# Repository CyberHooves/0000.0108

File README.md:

# 0000.0108
Headphone amplifier

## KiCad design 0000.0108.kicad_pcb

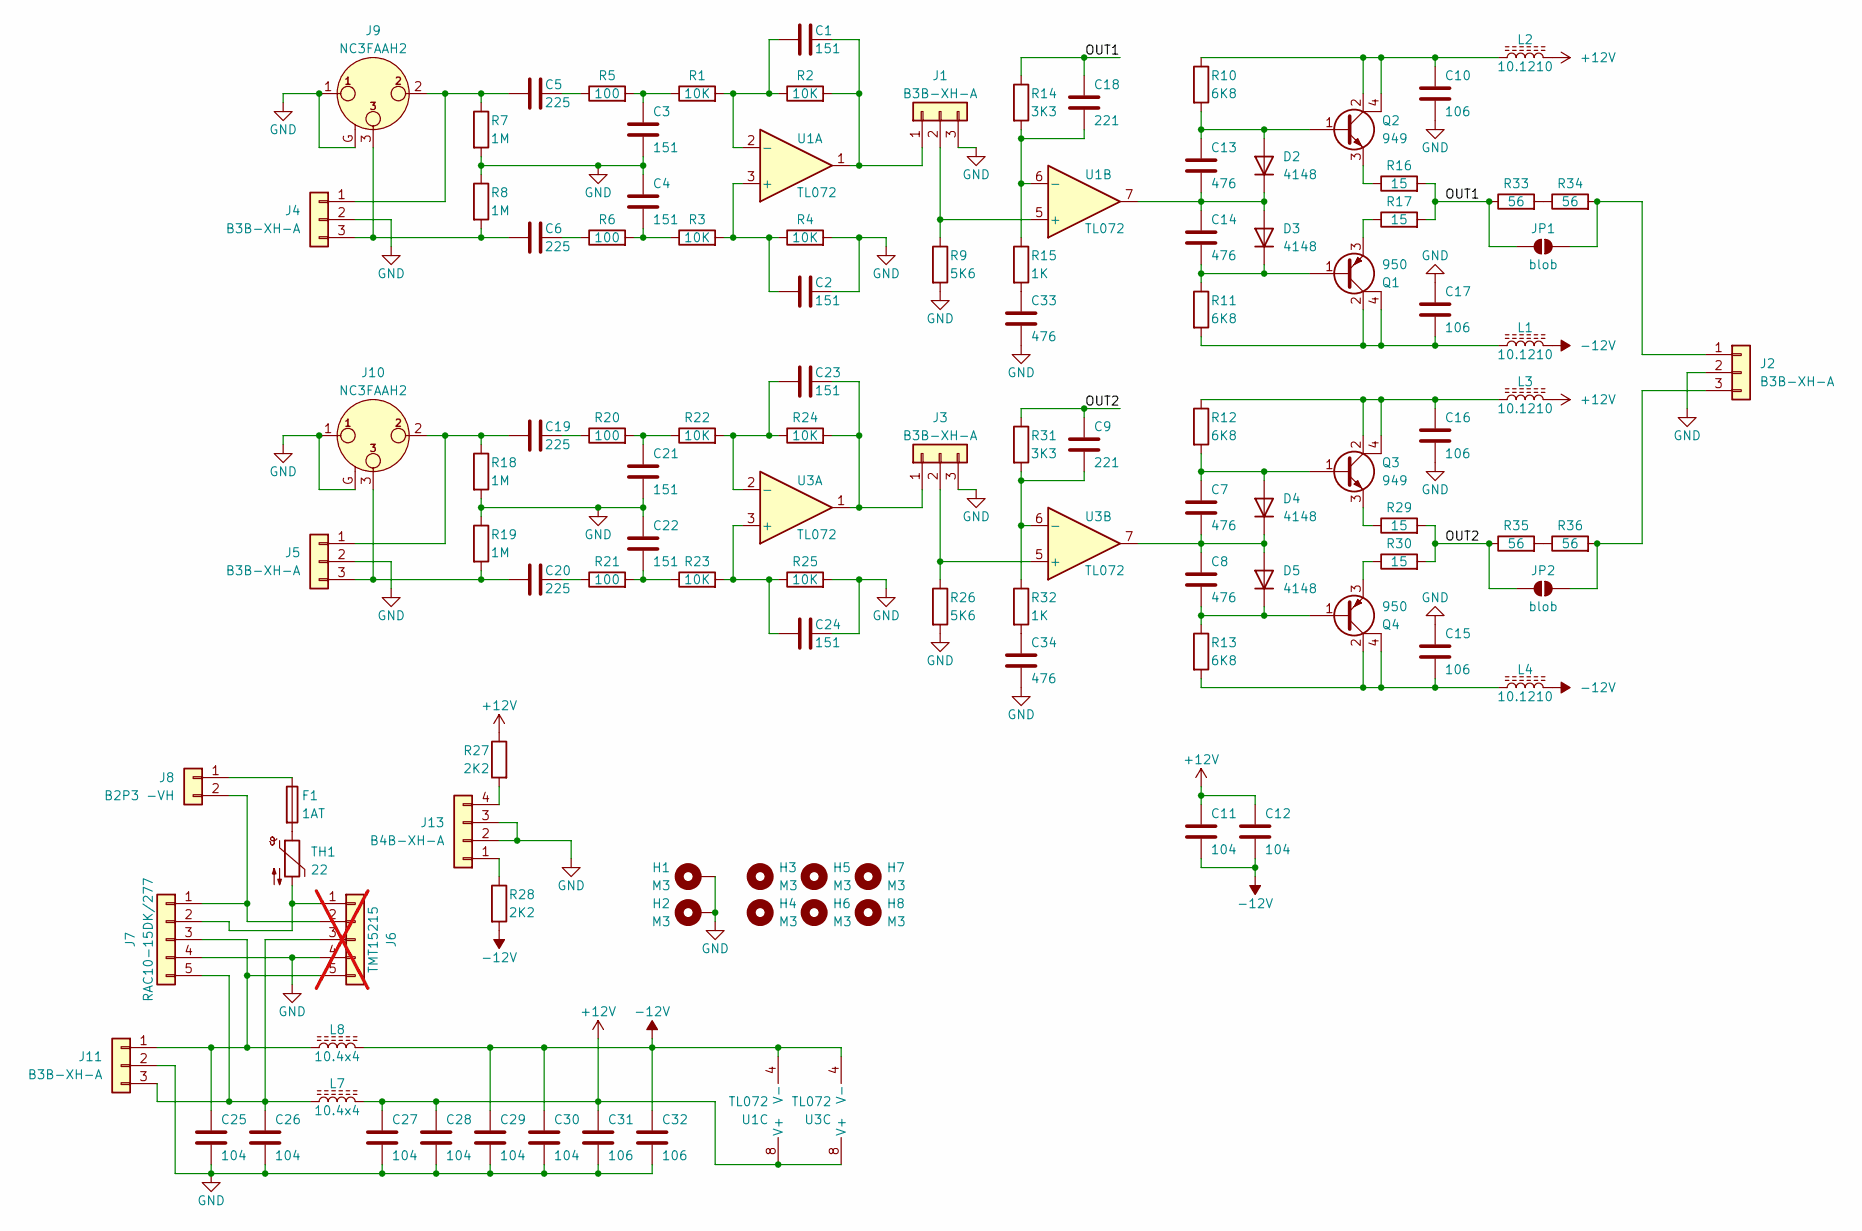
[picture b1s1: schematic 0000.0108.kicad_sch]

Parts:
C1, C2, C3, C4, C21, C22, C23, C24: 151; C_0805_2012Metric
C5, C6, C19, C20: 225; C_1210_3225Metric
C7, C8, C13, C14, C33, C34: 476; C_1210_3225Metric
C9, C18: 221; C_0805_2012Metric
C10, C15, C16, C17, C31, C32: 106; C_0805_2012Metric
C11, C12, C25, C26, C27, C28, C29, C30: 104; C_0805_2012Metric
D2, D3, D4, D5: 4148; D_SOD-123
F1: 1AT; Fuseholder_TR5_Littelfuse_No560_No460
H1, H2: M3; MountingHole_3.2mm_M3_Pad
H3, H4, H5, H6, H7, H8: M3; MountingHole_3.2mm_M3
J1, J2, J3, J4, J5, J11: B3B-XH-A; JST_XH_B3B-XH-AM_1x03_P2.50mm_Vertical
J6: TMT15215; PSU_TRACO_TMT152xx; not fitted
J7: RAC10-15DK/277; RECOM-RAC10
J8: B2P3 -VH; JST_VH_B2P3-VH_1x02_P7.92mm_Vertical
J9, J10: NC3FAAH2; Jack_XLR_Neutrik_NC3FAAH2_Horizontal
J13: B4B-XH-A; JST_XH_B4B-XH-AM_1x04_P2.50mm_Vertical
JP1, JP2: blob; SolderJumper-2_P1.3mm_Open_RoundedPad1.0x1.5mm
L1, L2, L3, L4: 10.1210; L_1210_3225Metric
L7, L8: 10.4x4; INDUCTOR_SMD_4x4
Q1, Q4: 950; SOT-223
Q2, Q3: 949; SOT-223
R1, R2, R3, R4, R22, R23, R24, R25: 10K; R_0805_2012Metric
R5, R6, R20, R21: 100; R_0805_2012Metric
R7, R8, R18, R19: 1M; R_0805_2012Metric
R9, R26: 5K6; R_0805_2012Metric
R10, R11, R12, R13: 6K8; R_0805_2012Metric
R14, R31: 3K3; R_0805_2012Metric
R15, R32: 1K; R_0805_2012Metric
R16, R17, R29, R30: 15; R_1210_3225Metric
R27, R28: 2K2; R_0805_2012Metric
R33, R34, R35, R36: 56; R_2512_6332Metric
TH1: 22; C_Disc_D10.5mm_W5.0mm_P5.00mm
U1, U3: TL072; SOIC-8_3.9x4.9mm_P1.27mm

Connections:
+12V: C11.1, C12.1, C27.1, C28.1, C31.1, L2.2, L3.2, L7.2, R27.1, U1.8 (V+), U3.8 (V+)
-12V: C11.2, C12.2, C29.1, C30.1, C32.1, L1.2, L4.2, L8.2, R28.2, U1.4 (V-), U3.4 (V-)
/OUT1: C18.1, JP1.1 (A), R14.1, R16.2, R17.2, R33.1
/OUT2: C9.1, JP2.1 (A), R29.2, R30.2, R31.1, R35.1
GND: C2.2, C3.2, C4.1, C10.2, C15.1, C16.2, C17.1, C21.2, C22.1, C24.2, C25.2, C26.2, C27.2, C28.2, C29.2, C30.2, C31.2, C32.2, C33.2, C34.2, H1.1, H2.1, J1.3, J2.2, J3.3, J4.2, J5.2, J6.4, J7.4, J9.1, J9.G, J10.1, J10.G, J11.2, J13.2, J13.3, R4.2, R7.2, R8.1, R9.2, R18.2, R19.1, R25.2, R26.2
unnamed: C3.1, R1.1, R5.2
unnamed: C4.2, R3.1, R6.2
unnamed: C5.2, R5.1
unnamed: C6.2, R6.1
unnamed: C10.1, L2.1, Q2.2 (C), Q2.4 (C), R10.1
unnamed: C15.2, L4.1, Q4.2 (C), Q4.4 (C), R13.2
unnamed: C16.1, L3.1, Q3.2 (C), Q3.4 (C), R12.1
unnamed: C17.2, L1.1, Q1.2 (C), Q1.4 (C), R11.2
unnamed: C19.2, R20.1
unnamed: C20.2, R21.1
unnamed: C21.1, R20.2, R22.1
unnamed: C22.2, R21.2, R23.1
unnamed: C33.1, R15.2
unnamed: C34.1, R32.2
unnamed: C13.1, D2.2 (A), Q2.1 (B), R10.2
unnamed: C13.2, C14.1, D2.1 (K), D3.2 (A), U1.7
unnamed: C14.2, D3.1 (K), Q1.1 (B), R11.1
unnamed: C7.1, D4.2 (A), Q3.1 (B), R12.2
unnamed: C7.2, C8.1, D4.1 (K), D5.2 (A), U3.7
unnamed: C8.2, D5.1 (K), Q4.1 (B), R13.1
unnamed: F1.2, TH1.1
unnamed: C1.2, J1.1, R2.2, U1.1
unnamed: J1.2, R9.1, U1.5 (+)
unnamed: J2.1, JP1.2 (B), R34.2
unnamed: J2.3, JP2.2 (B), R36.2
unnamed: C23.2, J3.1, R24.2, U3.1
unnamed: J3.2, R26.1, U3.5 (+)
unnamed: C5.1, J4.1, J9.2, R7.1
unnamed: C6.1, J4.3, J9.3, R8.2
unnamed: C19.1, J5.1, J10.2, R18.1
unnamed: C20.1, J5.3, J10.3, R19.2
unnamed: J6.1, J7.2, TH1.2
unnamed: J6.2, J7.1, J8.2
unnamed: F1.1, J8.1
unnamed: C25.1, J6.5, J7.3, J11.1, L8.1
unnamed: C26.1, J6.3, J7.5, J11.3, L7.1
unnamed: J13.1, R28.1
unnamed: J13.4, R27.2
unnamed: Q1.3 (E), R17.1
unnamed: Q2.3 (E), R16.1
unnamed: Q3.3 (E), R29.1
unnamed: Q4.3 (E), R30.1
unnamed: R33.2, R34.1
unnamed: R35.2, R36.1
unnamed: C2.1, R3.2, R4.1, U1.3 (+)
unnamed: C1.1, R1.2, R2.1, U1.2 (-)
unnamed: C18.2, R14.2, R15.1, U1.6 (-)
unnamed: C24.1, R23.2, R25.1, U3.3 (+)
unnamed: C23.1, R22.2, R24.1, U3.2 (-)
unnamed: C9.2, R31.2, R32.1, U3.6 (-)

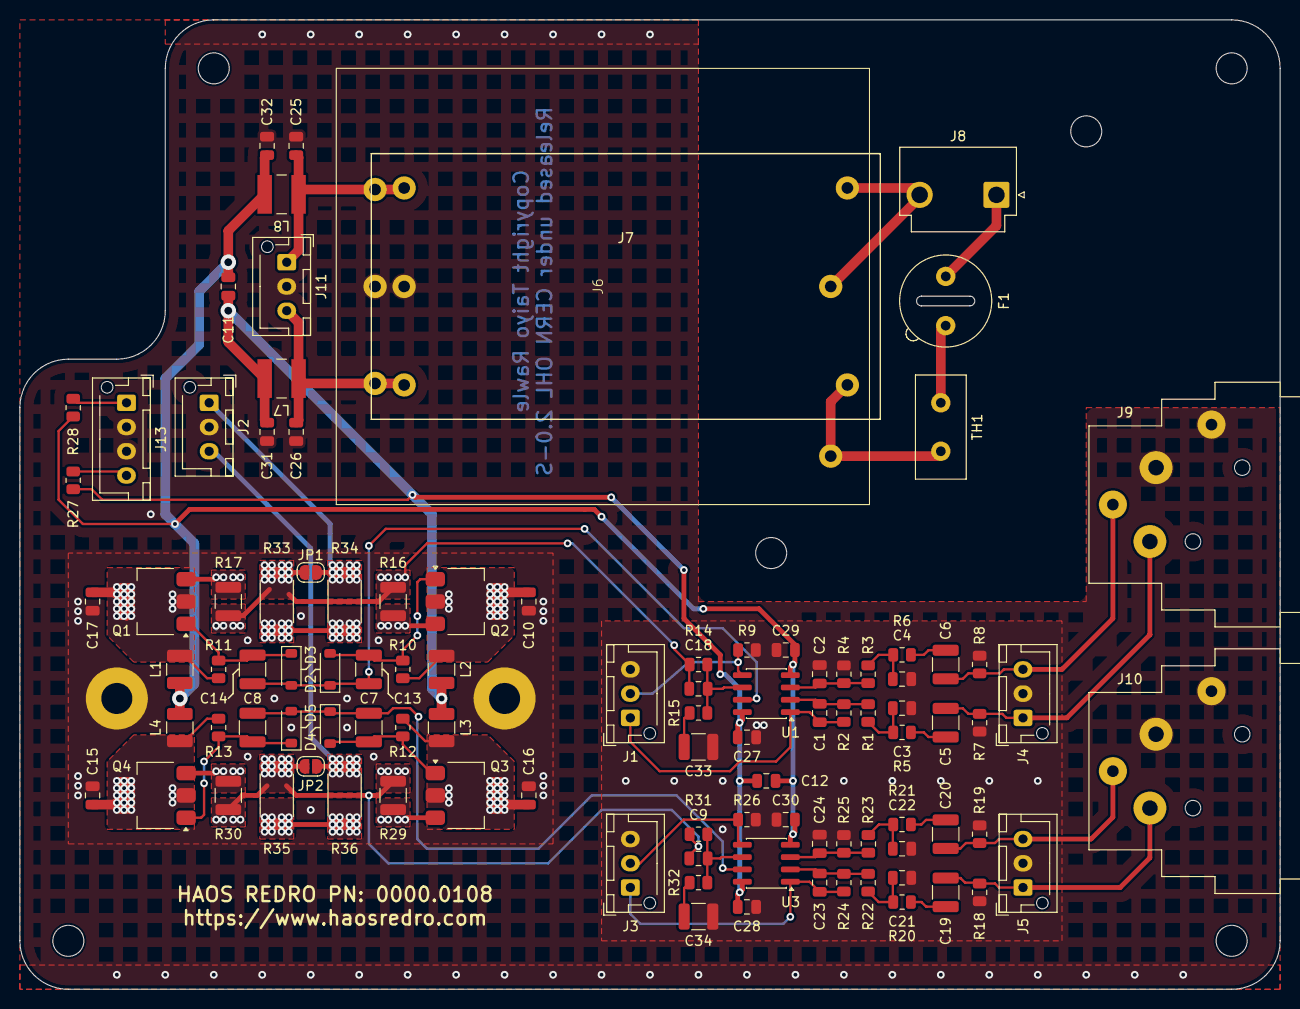
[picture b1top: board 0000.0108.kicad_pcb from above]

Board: 2 copper layers, 130.0 x 100.0 mm, 110 parts (0 on the bottom side), 55 nets.

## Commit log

2025-01-03 Updated missing or ambiguous component values. Added feed resistor bypass links.
2025-01-07 Minor housekeeping updates
2025-10-29 Changed XLR input connectors from NC3FAH to NC3FAH2 as the latter is compatible with both. NC3FAH has the shield/screw contact connected to pin 1. NC3FAH2 has this as a separate fourth pin.

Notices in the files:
0000.0108.kicad_pcb:
Copyright Taiyo Rawle
Released under CERN OHL 2.0-S
